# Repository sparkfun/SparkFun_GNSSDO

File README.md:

SparkPNT SXT / SXT-D
========================================

[*SparkPNT SXT (GNSSDO)*](https://www.sparkpnt.com/products/sxt-gnssdo)

Designed and manufactured in Boulder, Colorado, USA, the SparkPNT SXT GNSS Disciplined Oscillator (GNSSDO) and SXT-D GNSS Disciplined Oscillator Plus (GNSSDO+) are the perfect solution for your high-precision timing needs. Based around the multi-constellation, multi-frequency, L5-ready mosaic-T from Septentrio, these are our most accurate GNSS timing products to date. They feature a disciplined 10MHz oscillator: Digitally-Controlled Temperature-Controlled Crystal Oscillator (DCTCXO) on the SXT; Digitally-Controlled Double-Oven Crystal Oscillator (OCXO) on the SXT-D. The mosaic-T also has built-in on-module support for the Fugro AtomiChron L-band timing service.

Under the hood, the SXT and SXT-D are based on the mosaic-T GNSS module from Septentrio, plus the Espressif ESP32-WROVER processor (16MB flash, 8MB PSRAM). The mosaic-T has USB-C connectivity (with Ethernet-over-USB), multiple UARTs and supports full Ethernet connectivity. You can connect the mosaic-T directly to your Ethernet network - our product supports Power-over-Ethernet too. The ESP32 rides shotgun: disciplining the digitally-controlled oscillator and controlling the OLED display. Remote configuration is possible, the ESP32 console can be accessed via TCP. The SXT and SXT-D have multiple power options including USB-C, PoE and 9V-36V DC, making it easy to connect them to a battery-backed supply.

RTK Not Supported
--------------
The mosaic-T is a superb GNSS module designed for highly accurate timing applications. **But it does not support RTK. It can not be used as a RTK Rover or Base. RTCM output is not supported.**

Documentation
--------------

- **[Product Manual](http://docs.sparkfun.com/SparkFun_GNSSDO/)** - Product manual for the SXT(-D) GNSSDO(+) hosted by GitHub pages.<br>

*Need to download or print our hookup guide?*

- [Print *(Print to PDF)* from Single-Page View](http://docs.sparkfun.com/SparkFun_GNSSDO/print_view)

Firmware Update
-------------------

The **[/Firmware/Binaries](https://github.com/sparkfun/SparkFun_GNSSDO/tree/main/Firmware/Binaries)** folder contains the firmware binaries.

You can update or reload the firmware using the [SparkFun RTK Firmware Uploader](https://github.com/sparkfun/SparkFun_RTK_Firmware_Uploader).

Repository Contents
-------------------

- **[/docs](/docs/)** - Online documentation files
    - [assets](/docs/assets/) - Assets files
        - [board_files](/docs/assets/board_files/) - Files for the product design
            - [SXT Schematic](/docs/assets/board_files/schematic.pdf) (.pdf)
            - [SXT-D Schematic](/docs/assets/board_files/SparkPNT_GNSSDO_Plus_schematic) (.pdf)
            - [Dimensions](/docs/assets/board_files/dimensions.png) (.png)
            - [SXT KiCad files](/docs/assets/board_files/kicad_files.zip) (.zip)
            - [SXT-D KiCad files](/docs/assets/board_files/kicad_files_GNSSDO_Plus.zip) (.zip)
        - [img/hookup_guide/](/docs/assets/img/hookup_guide/) - Images for hookup guide documentation
- **[/Hardware](/Hardware/)** - KiCad design files
- **[/Hardware/Production](/Hardware/Production/)** - PCB panel production files
- **[/Front_Sticker](/Front_Sticker/)** - DXF and PDF files for the front sticker
- **[/Rear_Sticker](/Rear_Sticker/)** - DXF and PDF files for the rear sticker
- **[/Firmware](/Firmware/)** - Arduino source code and binaries for the firmware which runs on the ESP32-WROVER
- **[/Test_Sketches](/Test_Sketches/)** - Additional code used to validate and test the SXT
- **[/Documents](/Documents/)** - Component datasheets etc.

Product Variants
----------------

- [SXT](https://www.sparkpnt.com/products/sxt-gnssdo)- SXT (GNSSDO) v1.0, Initial Release
- [SXT-D](https://www.sparkpnt.com/products/sxt-d-gnssdo)- SXT-D (GNSSDO+) v1.0, Initial Release

Version History
---------------

- [v10](https://github.com/sparkfun/SparkFun_GNSSDO/releases/tag/v10) - Initial Release

License Information
-------------------

This product is ***open source***!

Please review the [LICENSE.md](./LICENSE.md) file for license information.

If you have any questions or concerns about licensing, please contact technical support on our [SparkPNT forums](https://community.sparkpnt.com).

Distributed as-is; no warranty is given.

- Your friends at SparkPNT.

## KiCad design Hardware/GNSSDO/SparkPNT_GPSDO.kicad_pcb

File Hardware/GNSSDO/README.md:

SparkPNT GNSSDO Design Files
=====================================

The files here are the KiCad schematic and PCB design files from SparkFun Electronics.

KiCad can be downloaded [here](https://www.kicad.org/).

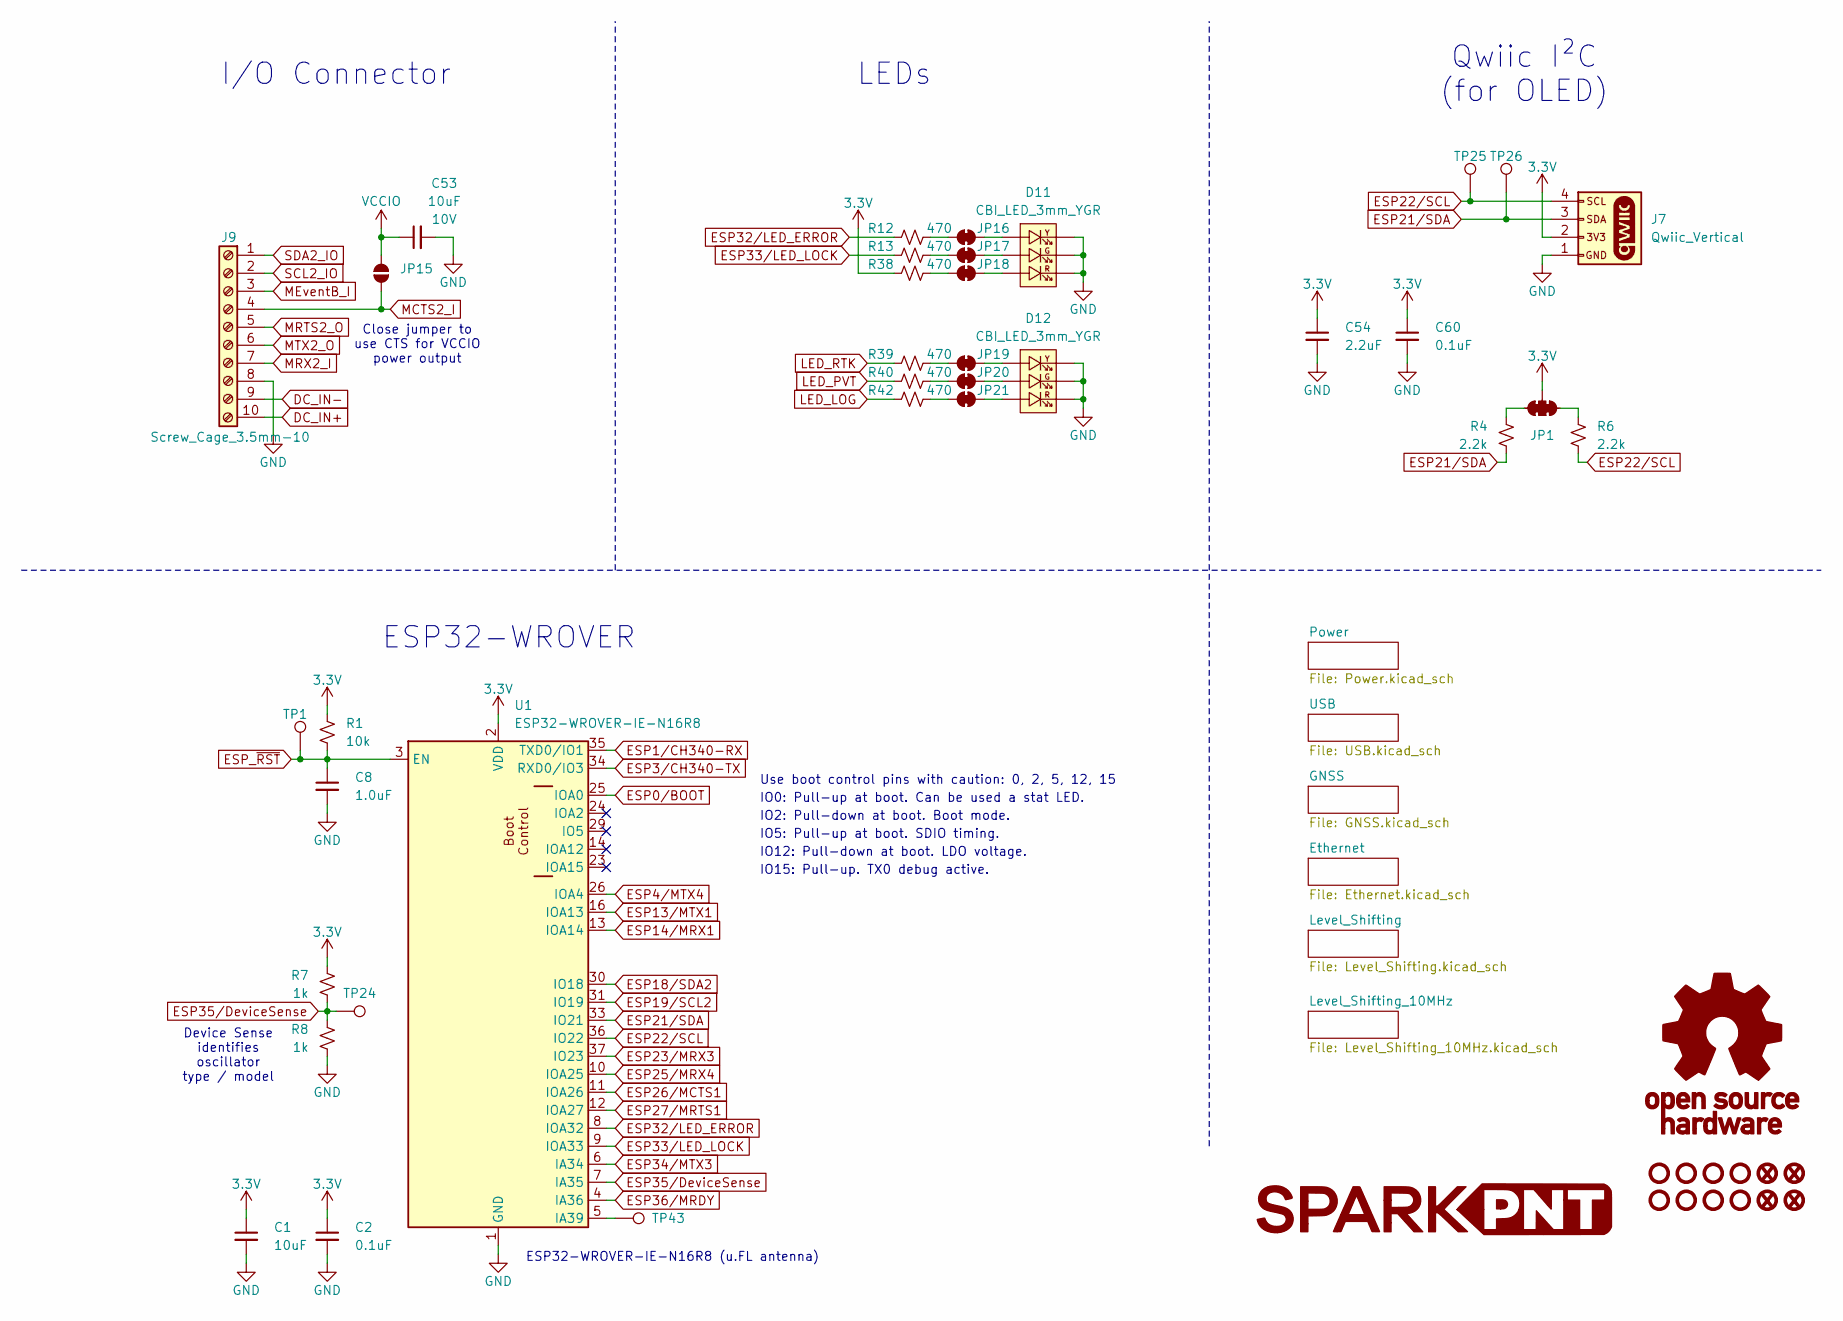
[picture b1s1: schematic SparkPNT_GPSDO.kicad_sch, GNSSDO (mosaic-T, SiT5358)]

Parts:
C1: 10uF; C_0603_1608Metric; Voltage 6.3V; Tolerance 20%
C2, C60: 0.1uF; C_0603_1608Metric; Voltage 25V; Tolerance 20%
C8: 1.0uF; C_0603_1608Metric; Voltage 16V; Tolerance 10%
C53: 10uF; C_0603_1608Metric; Voltage 10V; Tolerance 20%
C54: 2.2uF; C_0603_1608Metric; Voltage 10V; Tolerance 20%
D11, D12: CBI_LED_3mm_YGR; CBI_LED_Triple_3mm_PTH
FID1, FID2, FID3, FID4: Fiducial_0.5mm; Fiducial_0.5mm_Mask1mm
G1: OSHW_Logo; Creative_Commons_License
G2: LOGO
J7: Qwiic_Vertical; JST_1x04_P1.0mm_Vertical_SMD
J9: Screw_Cage_3.5mm-10; ScrewCage_1x10_P3.5mm_Horizontal
JP1: Jumper_3_NC-2_Trace
JP15: Jumper_2_NO
JP16, JP17, JP18, JP19, JP20, JP21: Jumper_2_NC_Trace
R1: 10k; R_0603_1608Metric
R4, R6: 2.2k; R_0603_1608Metric
R7, R8: 1k; R_0603_1608Metric
R12, R13, R38, R39, R40, R42: 470; R_0603_1608Metric
ST1, ST2, ST3, ST4, ST5, ST6, ST7, ST8: Standoff
TP1, TP24, TP25, TP26, TP43: PTH; 1x01_P2.54mm
U1: ESP32-WROVER-IE-N16R8; ESP32-WROVER-E-IE

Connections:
3.3V: C1.1, C2.1, C54.1, C60.1, J7.2, JP1.2 (B), R1.2, R7.2, R38.1, U1.2 (VDD); also elsewhere on the board
DC_IN+: J9.10 (Pin_1); also elsewhere on the board
DC_IN-: J9.9 (Pin_1); also elsewhere on the board
ESP0/BOOT: U1.25 (IOA0); also elsewhere on the board
ESP1/CH340-RX: U1.35 (TXD0/IO1); also elsewhere on the board
ESP3/CH340-TX: U1.34 (RXD0/IO3); also elsewhere on the board
ESP4/MTX4: U1.26 (IOA4); also elsewhere on the board
ESP13/MTX1: U1.16 (IOA13); also elsewhere on the board
ESP14/MRX1: U1.13 (IOA14); also elsewhere on the board
ESP18/SDA2: U1.30 (IO18); also elsewhere on the board
ESP19/SCL2: U1.31 (IO19); also elsewhere on the board
ESP21/SDA: J7.3, R4.2, TP26.1 (1_1), U1.33 (IO21)
ESP22/SCL: J7.4, R6.2, TP25.1 (1_1), U1.36 (IO22)
ESP23/MRX3: U1.37 (IO23); also elsewhere on the board
ESP25/MRX4: U1.10 (IOA25); also elsewhere on the board
ESP26/MCTS1: U1.11 (IOA26); also elsewhere on the board
ESP27/MRTS1: U1.12 (IOA27); also elsewhere on the board
ESP32/LED_ERROR: R12.1, U1.8 (IOA32)
ESP33/LED_LOCK: R13.1, U1.9 (IOA33)
ESP34/MTX3: U1.6 (IA34); also elsewhere on the board
ESP35/DeviceSense: R7.1, R8.2, TP24.1 (1_1), U1.7 (IA35)
ESP36/MRDY: U1.4 (IA36); also elsewhere on the board
ESP_~RST: C8.1, R1.1, TP1.1 (1_1), U1.3 (EN); also elsewhere on the board
GND: C1.2, C2.2, C8.2, C53.2, C54.2, C60.2, D11.CATHODE_1, D11.CATHODE_2, D11.CATHODE_3, D12.CATHODE_1, D12.CATHODE_2, D12.CATHODE_3, J7.1, J9.8 (Pin_1), R8.1, U1.1 (GND), U1.15 (GND), U1.38 (GND), U1.39.1 (GND), U1.39.2 (GND), U1.39.3 (GND), U1.39.4 (GND), U1.39.5 (GND), U1.39.6 (GND), U1.39.7 (GND), U1.39.8 (GND), U1.39.9 (GND); also elsewhere on the board
LED_LOG: R42.1; also elsewhere on the board
LED_PVT: R40.1; also elsewhere on the board
LED_RTK: R39.1; also elsewhere on the board
MCTS2_I: J9.4, JP15.1 (A); also elsewhere on the board
MEventB_I: J9.3; also elsewhere on the board
MRTS2_O: J9.5 (Pin_3); also elsewhere on the board
MRX2_I: J9.7 (Pin_2); also elsewhere on the board
MTX2_O: J9.6 (Pin_4); also elsewhere on the board
unnamed: JP1.1 (A), R6.1
unnamed: JP1.3 (C), R4.1
unnamed: JP16.1 (A), R12.2
unnamed: D11.ANODE_1, JP16.2 (B)
unnamed: JP17.1 (A), R13.2
unnamed: D11.ANODE_2, JP17.2 (B)
unnamed: JP18.1 (A), R38.2
unnamed: D11.ANODE_3, JP18.2 (B)
unnamed: JP19.1 (A), R39.2
unnamed: D12.ANODE_1, JP19.2 (B)
unnamed: JP20.1 (A), R40.2
unnamed: D12.ANODE_2, JP20.2 (B)
unnamed: JP21.1 (A), R42.2
unnamed: D12.ANODE_3, JP21.2 (B)
unnamed: TP43.1 (1_1), U1.5 (IA39)
SCL2_IO: J9.2; also elsewhere on the board
SDA2_IO: J9.1; also elsewhere on the board
VCCIO: C53.1, JP15.2 (B); also elsewhere on the board

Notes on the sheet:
IO15: Pull-up. TX0 debug active.
IO2: Pull-down at boot. Boot mode.
ESP32-WROVER
IO0: Pull-up at boot. Can be used a stat LED.
LEDs
Qwiic I²C (for OLED)
Device Sense identifies oscillator type / model
Close jumper to use CTS for VCCIO power output
IO5: Pull-up at boot. SDIO timing.
I/O Connector
Use boot control pins with caution: 0, 2, 5, 12, 15
ESP32-WROVER-IE-N16R8 (u.FL antenna)
IO12: Pull-down at boot. LDO voltage.

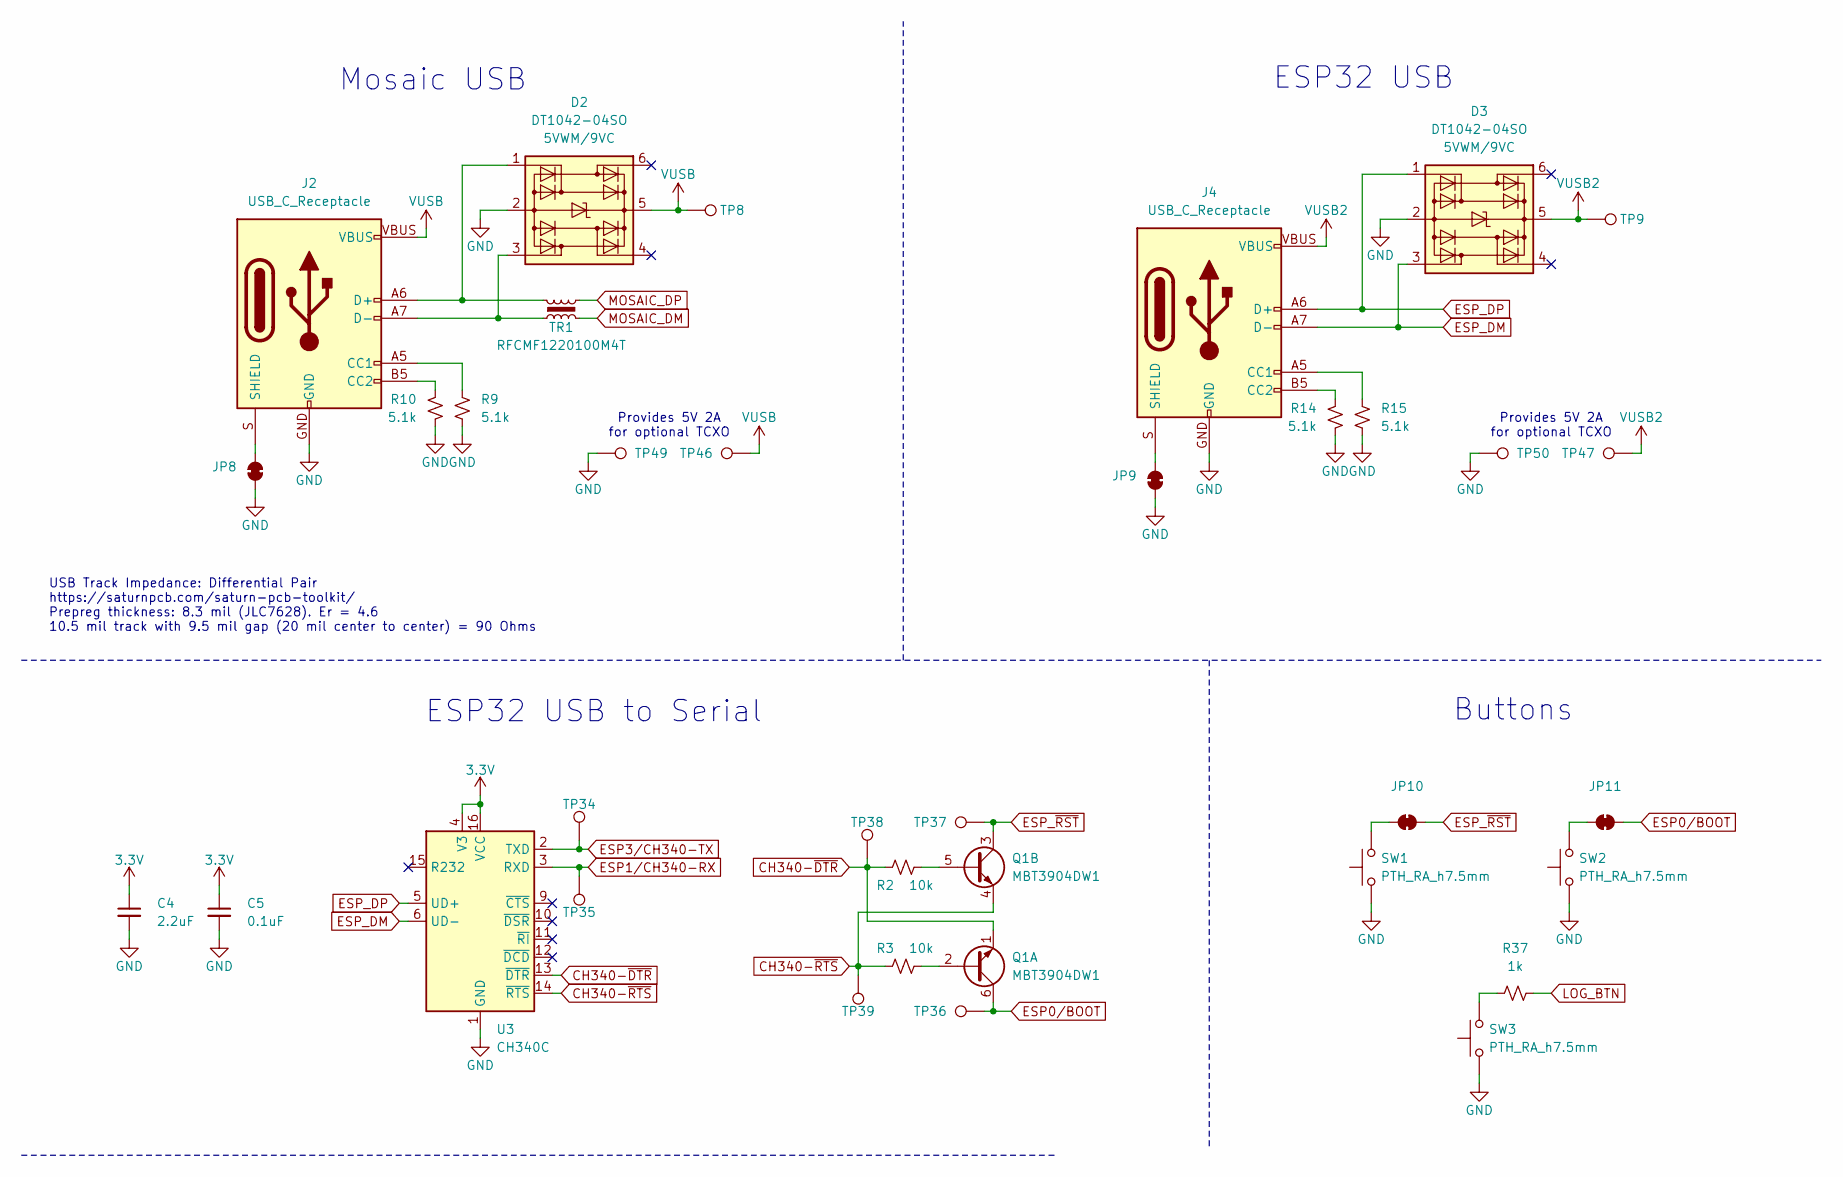
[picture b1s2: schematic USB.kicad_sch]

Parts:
C4: 2.2uF; C_0603_1608Metric; Voltage 10V; Tolerance 20%
C5: 0.1uF; C_0603_1608Metric; Voltage 25V; Tolerance 20%
D2, D3: DT1042-04SO; SOT23-6; Rating 5VWM/9VC
J2, J4: USB_C_Receptacle; USB-C_16
JP8, JP9, JP10, JP11: Jumper_2_NC_Trace
Q1: MBT3904DW1; SOT-363_SC-70-6
R2, R3: 10k; R_0603_1608Metric
R9, R10, R14, R15: 5.1k; R_0603_1608Metric
R37: 1k; R_0603_1608Metric
SW1, SW2, SW3: PTH_RA_h7.5mm; Push_PTH_RA_8-020_h7.5mm; Mfg Part# 8-020 TS H = 7.5mm
TP8, TP9, TP34, TP35, TP36, TP37, TP38, TP39, TP46, TP47, TP49, TP50: PTH; 1x01_P2.54mm
TR1: RFCMF1220100M4T; Choke_100MHz_USB
U3: CH340C; SO-16

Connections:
3.3V: C4.1, C5.1, U3.4 (V3), U3.16 (VCC); also elsewhere on the board
CH340-~DTR: Q1.1 (E1), R2.1, TP38.1 (1_1), U3.13 (~DTR)
CH340-~RTS: Q1.4 (E2), R3.1, TP39.1 (1_1), U3.14 (~RTS)
ESP0/BOOT: JP11.2 (B), Q1.6 (C1), TP36.1 (1_1); also elsewhere on the board
ESP1/CH340-RX: TP35.1 (1_1), U3.3 (RXD); also elsewhere on the board
ESP3/CH340-TX: TP34.1 (1_1), U3.2 (TXD); also elsewhere on the board
ESP_DM: D3.3 (I/O2), J4.A7 (D-), J4.B7 (D-), U3.6 (UD-)
ESP_DP: D3.1 (I/O1), J4.A6 (D+), J4.B6 (D+), U3.5 (UD+)
ESP_~RST: JP10.2 (B), Q1.3 (C2), TP37.1 (1_1); also elsewhere on the board
GND: C4.2, C5.2, D2.2 (GND), D3.2 (GND), J2.GND, J4.GND, JP8.1 (A), JP9.1 (A), R9.2, R10.2, R14.2, R15.2, SW1.1, SW2.1, SW3.1, TP49.1 (1_1), TP50.1 (1_1), U3.1 (GND); also elsewhere on the board
LOG_BTN: R37.2; also elsewhere on the board
MOSAIC_DM: TR1.2; also elsewhere on the board
MOSAIC_DP: TR1.4; also elsewhere on the board
unnamed: D2.1 (I/O1), J2.A6 (D+), J2.B6 (D+), TR1.3
unnamed: D2.3 (I/O2), J2.A7 (D-), J2.B7 (D-), TR1.1
unnamed: J2.A5 (CC1), R9.1
unnamed: J2.B5 (CC2), R10.1
unnamed: J2.S (SHIELD), JP8.2 (B)
unnamed: J4.A5 (CC1), R15.1
unnamed: J4.B5 (CC2), R14.1
unnamed: J4.S (SHIELD), JP9.2 (B)
unnamed: JP10.1 (A), SW1.2
unnamed: JP11.1 (A), SW2.2
unnamed: Q1.2 (B1), R3.2
unnamed: Q1.5 (B2), R2.2
unnamed: R37.1, SW3.2
VUSB: D2.5 (VCC), J2.VBUS, TP8.1 (1_1), TP46.1 (1_1); also elsewhere on the board
VUSB2: D3.5 (VCC), J4.VBUS, TP9.1 (1_1), TP47.1 (1_1); also elsewhere on the board

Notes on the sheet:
ESP32 USB to Serial
Mosaic USB
Provides 5V 2A for optional TCXO
Buttons
ESP32 USB
USB Track Impedance: Differential Pair https://saturnpcb.com/saturn-pcb-toolkit/ Prepreg thickness: 8.3 mil (JLC7628). Er = 4.6 10.5 mil track with 9.5 mil gap (20 mil center to center) = 90 Ohms

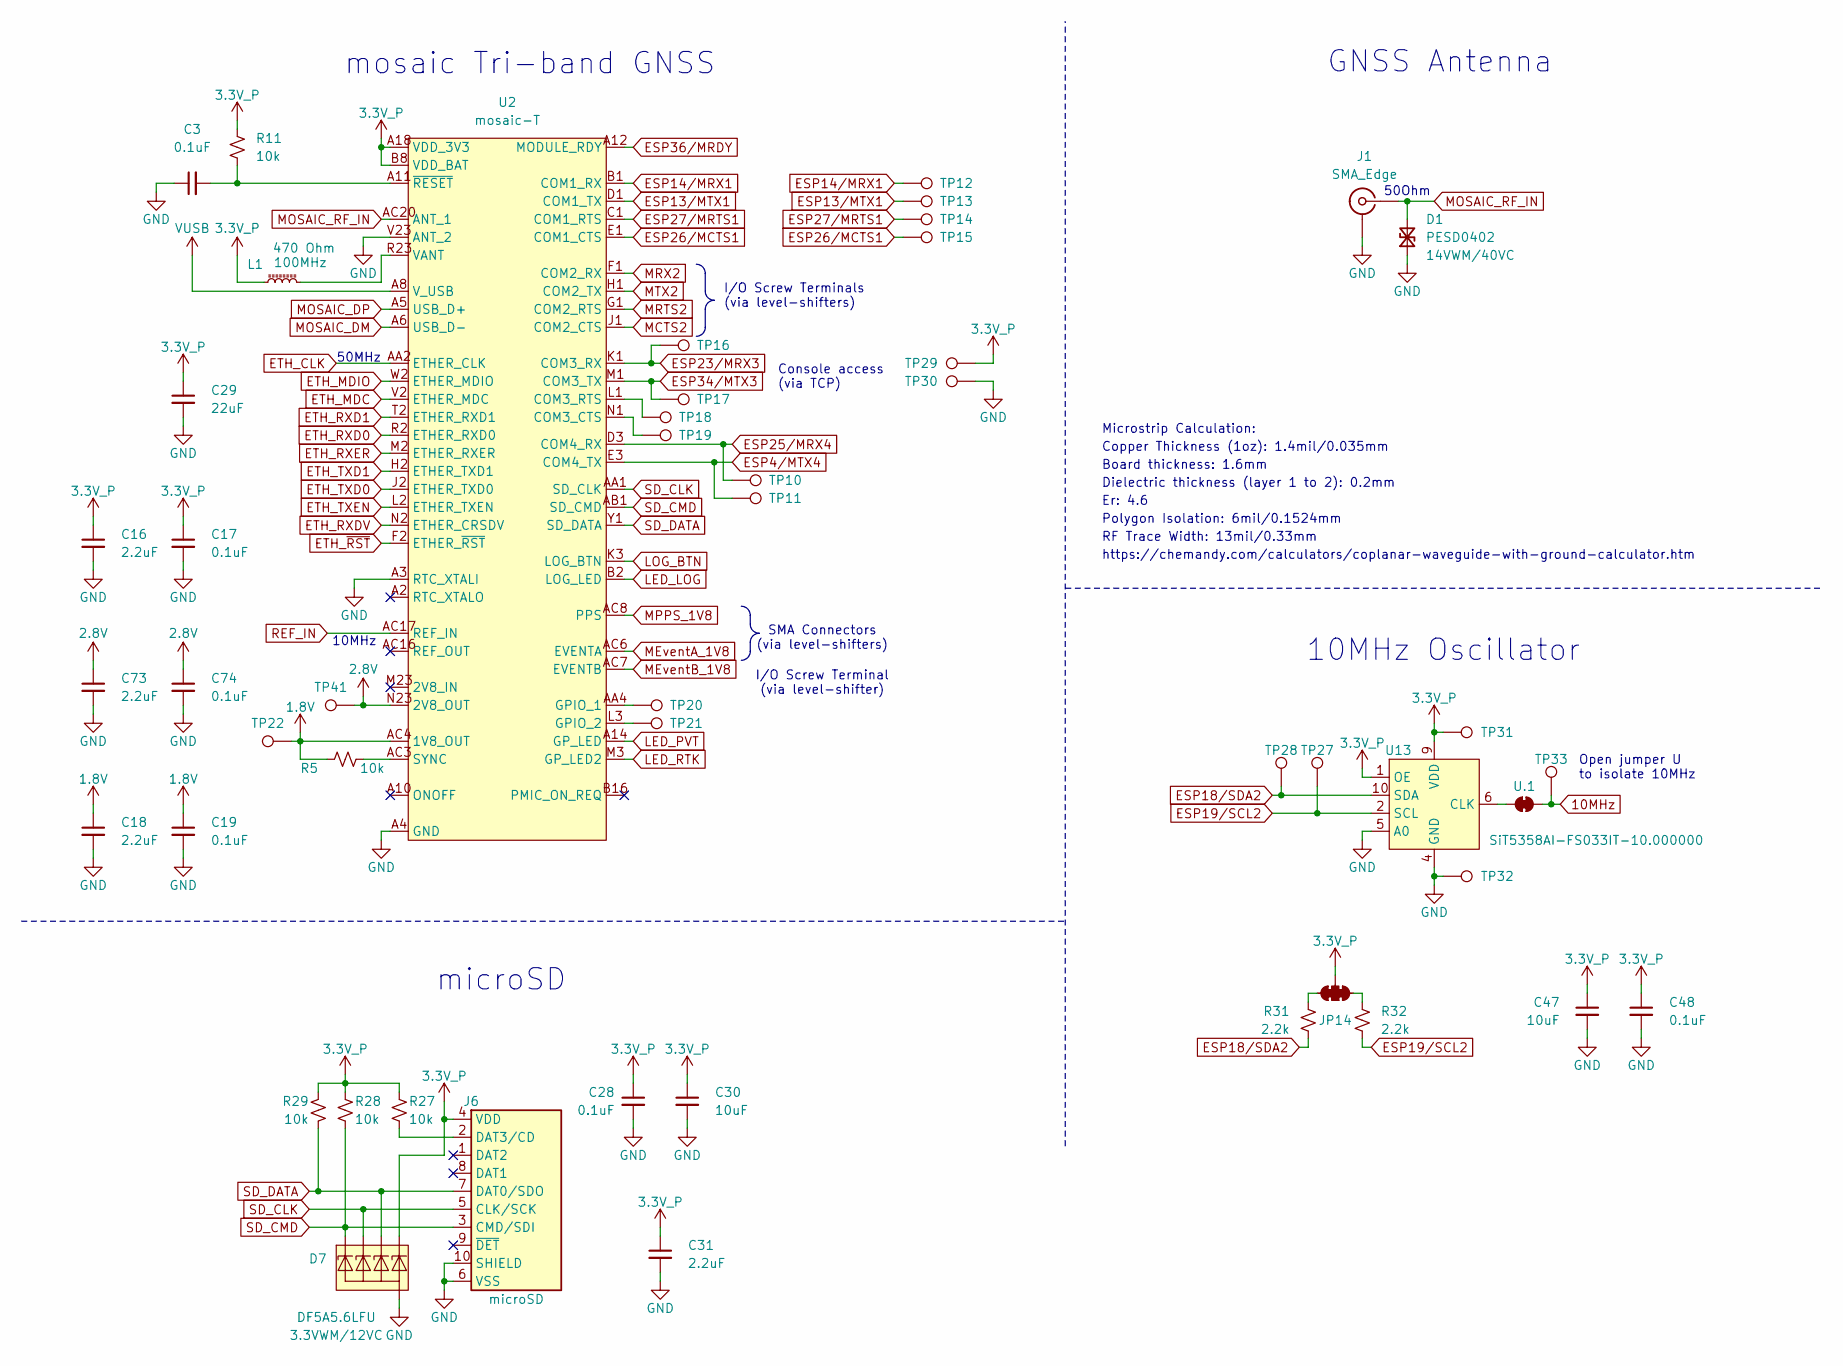
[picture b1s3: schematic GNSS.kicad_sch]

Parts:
C3, C17, C19, C28, C48, C74: 0.1uF; C_0603_1608Metric; Voltage 25V; Tolerance 20%
C16, C18, C31, C73: 2.2uF; C_0603_1608Metric; Voltage 10V; Tolerance 20%
C29: 22uF; C_0603_1608Metric; Voltage 6.3V; Tolerance 20%
C30, C47: 10uF; C_0603_1608Metric; Voltage 10V; Tolerance 20%
D1: PESD0402; C_0402_1005Metric; Rating 14VWM/40VC
D7: DF5A5.6LFU; SOT-353; Rating 3.3VWM/12VC
J1: SMA_Edge; SMA_Edge_6.3mm
J6: microSD; microSD_External_Pin
JP14: Jumper_3_NC-2_Trace
L1: 470 Ohm; C_0603_1608Metric
R5, R11, R27, R28, R29: 10k; R_0603_1608Metric
R31, R32: 2.2k; R_0603_1608Metric
TP10, TP11, TP12, TP13, TP14, TP15, TP16, TP17, TP18, TP19, TP20, TP21, TP22, TP27, TP28, TP29, TP30, TP31, TP32, TP33, TP41: PTH; 1x01_P2.54mm
U2: mosaic-T; Septentrio_mosaic_LGA
U13: SiT5358AI-FS033IT-10.000000; Ceramic_QFN_5.0x3.2mm-10
U.1: Jumper_2_NC_Trace

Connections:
1.8V: C18.1, C19.1, R5.1, TP22.1 (1_1), U2.AC4 (1V8_OUT); also elsewhere on the board
2.8V: C73.1, C74.1, TP41.1 (1_1), U2.N23 (2V8_OUT); also elsewhere on the board
3.3V_P: C16.1, C17.1, C28.1, C29.1, C30.1, C31.1, C47.1, C48.1, D7.5 (K4), J6.4 (VDD), JP14.2 (B), L1.1, R11.1, R27.1, R28.1, R29.1, TP29.1 (1_1), TP31.1 (1_1), U2.A18 (VDD_3V3), U2.A19 (VDD_3V3), U2.A20 (VDD_3V3), U2.B8 (VDD_BAT), U2.B18 (VDD_3V3), U2.B19 (VDD_3V3), U2.B20 (VDD_3V3), U2.C18 (VDD_3V3), U2.C19 (VDD_3V3), U2.C20 (VDD_3V3), U13.1 (OE), U13.9 (VDD); also elsewhere on the board
10MHz: TP33.1 (1_1), U.1.2 (B); also elsewhere on the board
ESP4/MTX4: TP11.1 (1_1), U2.E3 (COM4_TX); also elsewhere on the board
ESP13/MTX1: TP13.1 (1_1), U2.D1 (COM1_TX); also elsewhere on the board
ESP14/MRX1: TP12.1 (1_1), U2.B1 (COM1_RX); also elsewhere on the board
ESP18/SDA2: R31.1, TP28.1 (1_1), U13.10 (SDA); also elsewhere on the board
ESP19/SCL2: R32.1, TP27.1 (1_1), U13.2 (SCL); also elsewhere on the board
ESP23/MRX3: TP16.1 (1_1), U2.K1 (COM3_RX); also elsewhere on the board
ESP25/MRX4: TP10.1 (1_1), U2.D3 (COM4_RX); also elsewhere on the board
ESP26/MCTS1: TP15.1 (1_1), U2.E1 (COM1_CTS); also elsewhere on the board
ESP27/MRTS1: TP14.1 (1_1), U2.C1 (COM1_RTS); also elsewhere on the board
ESP34/MTX3: TP17.1 (1_1), U2.M1 (COM3_TX); also elsewhere on the board
ESP36/MRDY: U2.A12 (MODULE_RDY); also elsewhere on the board
ETH_CLK: U2.AA2 (ETHER_CLK); also elsewhere on the board
ETH_MDC: U2.V2 (ETHER_MDC); also elsewhere on the board
ETH_MDIO: U2.W2 (ETHER_MDIO); also elsewhere on the board
ETH_RXD0: U2.R2 (ETHER_RXD0); also elsewhere on the board
ETH_RXD1: U2.T2 (ETHER_RXD1); also elsewhere on the board
ETH_RXDV: U2.N2 (ETHER_CRSDV); also elsewhere on the board
ETH_RXER: U2.M2 (ETHER_RXER); also elsewhere on the board
ETH_TXD0: U2.J2 (ETHER_TXD0); also elsewhere on the board
ETH_TXD1: U2.H2 (ETHER_TXD1); also elsewhere on the board
ETH_TXEN: U2.L2 (ETHER_TXEN); also elsewhere on the board
ETH_~RST: U2.F2 (ETHER_~RST); also elsewhere on the board
GND: C3.1, C16.2, C17.2, C18.2, C19.2, C28.2, C29.2, C30.2, C31.2, C47.2, C48.2, C73.2, C74.2, D1.1 (A1), D7.2 (A), J1.2 (Ext), J6.6 (VSS), J6.10 (SHIELD), TP30.1 (1_1), TP32.1 (1_1), U2.A3 (RTC_XTALI), U2.A4 (GND), U2.A7 (GND), U2.A15 (GND), U2.A16 (GND), U2.A17 (GND), U2.A21 (GND), U2.A22 (GND), U2.A23 (GND), U2.AA13 (GND), U2.AA14 (GND), U2.AA15 (GND), U2.AA16 (GND), U2.AA17 (GND), U2.AA18 (GND), U2.AA19 (GND), U2.AA20 (GND), U2.AA21 (GND), U2.AA22 (GND), U2.AA23 (GND), U2.AB2 (GND), U2.AB3 (GND), U2.AB4 (GND), U2.AB5 (GND), U2.AB6 (GND), U2.AB7 (GND), U2.AB8 (GND), U2.AB13 (GND), U2.AB14 (GND), U2.AB15 (GND), U2.AB16 (GND), U2.AB17 (GND), U2.AB18 (GND), U2.AB19 (GND), U2.AB20 (GND), U2.AB21 (GND), U2.AB22 (GND), U2.AB23 (GND), U2.AC13 (GND), U2.AC15 (GND), U2.AC18 (GND), U2.AC19 (GND), U2.AC21 (GND), U2.AC22 (GND), U2.AC23 (GND), U2.B4 (GND), U2.B5 (GND), U2.B6 (GND), U2.B7 (GND), U2.B13 (GND), U2.B17 (GND), U2.B21 (GND), U2.C4 (GND), U2.C7 (GND), U2.C15 (GND), U2.C16 (GND), U2.C17 (GND), U2.C23 (GND), U2.D2 (GND), U2.D21 (GND), U2.D22 (GND), U2.D23 (GND), U2.E2 (GND), U2.E21 (GND), U2.E22 (GND), U2.E23 (GND), U2.F21 (GND), U2.F22 (GND), U2.F23 (GND), U2.G2 (GND), U2.G21 (GND), U2.G23 (GND), U2.H21 (GND), U2.H22 (GND), U2.H23 (GND), U2.J21 (GND), U2.J22 (GND), U2.J23 (GND), U2.K2 (GND), U2.K21 (GND), U2.K22 (GND), U2.K23 (GND), U2.L21 (GND), U2.L22 (GND), U2.L23 (GND), U2.M21 (GND), U2.M22 (GND), U2.N21 (GND), U2.N22 (GND), U2.P1 (GND), U2.P2 (GND), U2.P3 (GND), U2.P21 (GND), U2.P22 (GND), U2.R3 (GND), U2.R21 (GND), U2.R22 (GND), U2.T21 (GND), U2.T22 (GND), U2.T23 (GND), U2.U2 (GND), U2.U21 (GND), U2.U22 (GND), U2.U23 (GND), U2.V21 (GND), U2.V22 (GND), U2.V23 (ANT_2), U2.W21 (GND), U2.W22 (GND), U2.W23 (GND), U2.Y2 (GND), U2.Y21 (GND), U2.Y22 (GND), U2.Y23 (GND), U13.4 (GND), U13.5 (A0); also elsewhere on the board
LED_LOG: U2.B2 (LOG_LED); also elsewhere on the board
LED_PVT: U2.A14 (GP_LED); also elsewhere on the board
LED_RTK: U2.M3 (GP_LED2); also elsewhere on the board
LOG_BTN: U2.K3 (LOG_BTN); also elsewhere on the board
MCTS2: U2.J1 (COM2_CTS); also elsewhere on the board
MEventA_1V8: U2.AC6 (EVENTA); also elsewhere on the board
MEventB_1V8: U2.AC7 (EVENTB); also elsewhere on the board
MOSAIC_DM: U2.A6 (USB_D-); also elsewhere on the board
MOSAIC_DP: U2.A5 (USB_D+); also elsewhere on the board
MOSAIC_RF_IN: D1.2 (A2), J1.1 (In), U2.AC20 (ANT_1)
MPPS_1V8: U2.AC8 (PPS); also elsewhere on the board
MRTS2: U2.G1 (COM2_RTS); also elsewhere on the board
MRX2: U2.F1 (COM2_RX); also elsewhere on the board
MTX2: U2.H1 (COM2_TX); also elsewhere on the board
unnamed: J6.2 (DAT3/CD), R27.2
unnamed: JP14.1 (A), R32.2
unnamed: JP14.3 (C), R31.2
unnamed: TP19.1 (1_1), U2.N1 (COM3_CTS)
unnamed: TP18.1 (1_1), U2.L1 (COM3_RTS)
unnamed: TP20.1 (1_1), U2.AA4 (GPIO_1)
unnamed: TP21.1 (1_1), U2.L3 (GPIO_2)
unnamed: R5.2, U2.AC3 (SYNC)
unnamed: C3.2, R11.2, U2.A11 (~RESET)
unnamed: U13.6 (CLK), U.1.1 (A)
REF_IN: U2.AC17 (REF_IN); also elsewhere on the board
SD_CLK: D7.3 (K2), J6.5 (CLK/SCK), U2.AA1 (SD_CLK)
SD_CMD: D7.1 (K1), J6.3 (CMD/SDI), R28.2, U2.AB1 (SD_CMD)
SD_DATA: D7.4 (K3), J6.7 (DAT0/SDO), R29.2, U2.Y1 (SD_DATA)
VANT: L1.2, U2.P23 (VANT), U2.R23 (VANT)
VUSB: U2.A8 (V_USB); also elsewhere on the board

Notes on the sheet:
Er: 4.6
Polygon Isolation: 6mil/0.1524mm
10MHz
Console access (via TCP)
SMA Connectors (via level-shifters)
10MHz Oscillator
Dielectric thickness (layer 1 to 2): 0.2mm
Board thickness: 1.6mm
Open jumper U to isolate 10MHz
mosaic Tri-band GNSS
Microstrip Calculation:
50Ohm
I/O Screw Terminals (via level-shifters)
https://chemandy.com/calculators/coplanar-waveguide-with-ground-calculator.htm
Copper Thickness (1oz): 1.4mil/0.035mm
I/O Screw Terminal (via level-shifter)
50MHz
GNSS Antenna
microSD
RF Trace Width: 13mil/0.33mm

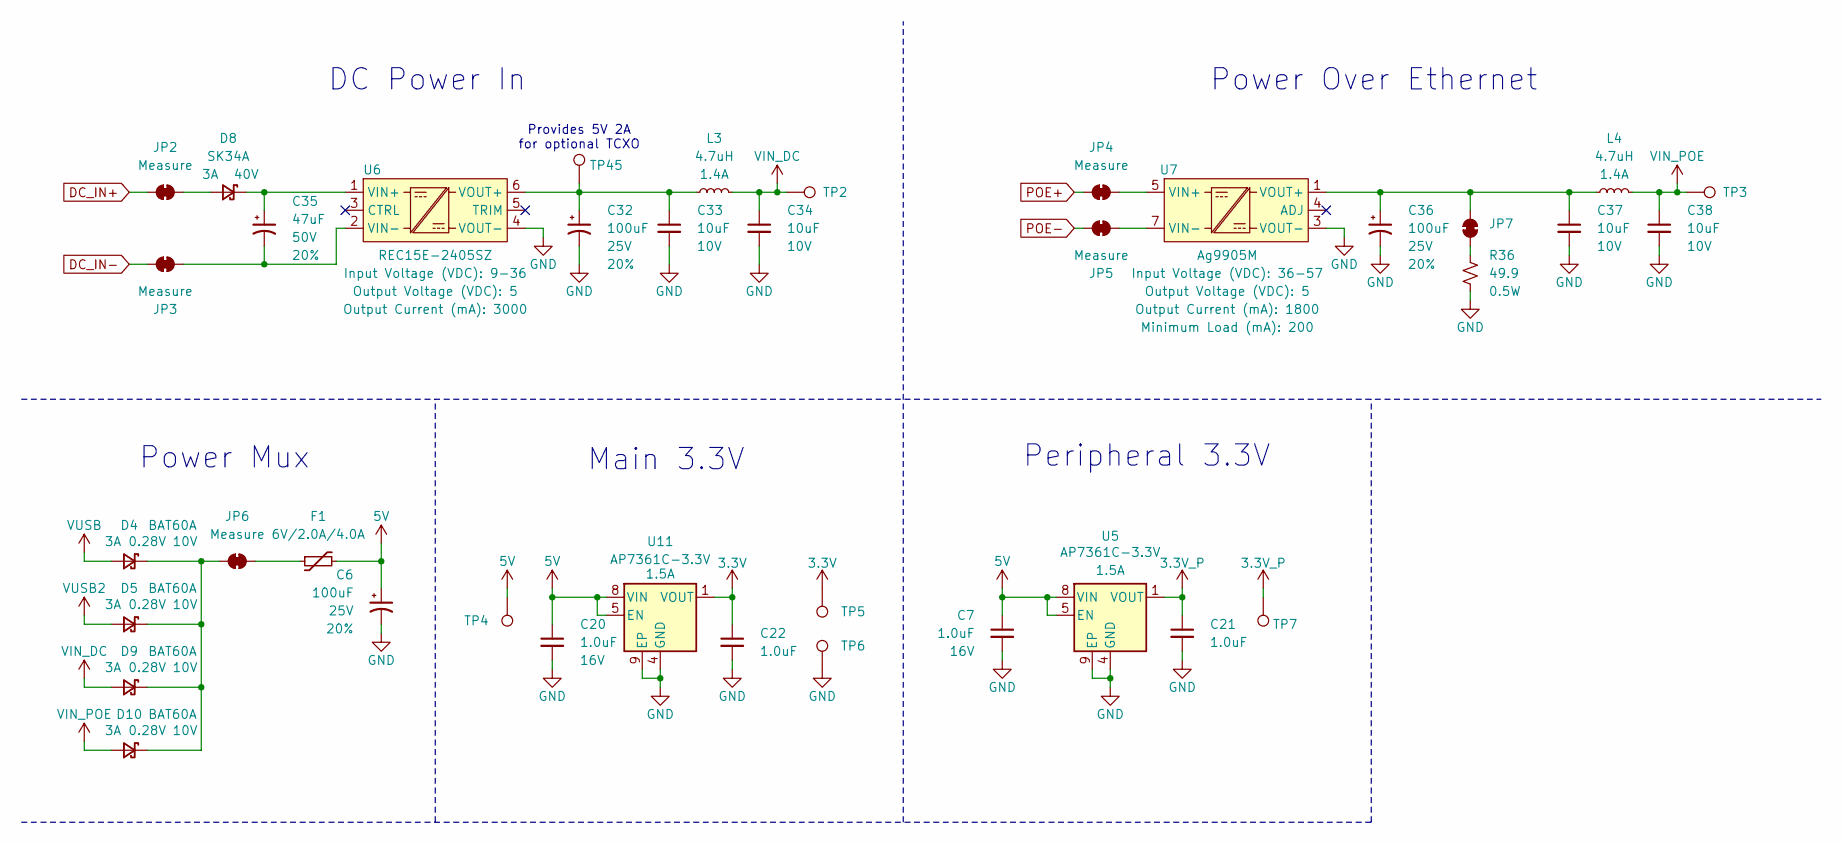
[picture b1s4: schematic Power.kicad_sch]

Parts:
C6, C32, C36: 100uF; Panasonic_D; Voltage 25V; Tolerance 20%
C7, C20, C21, C22: 1.0uF; C_0603_1608Metric; Voltage 16V; Tolerance 10%
C33, C34, C37, C38: 10uF; C_0603_1608Metric; Voltage 10V; Tolerance 20%
C35: 47uF; Panasonic_D; Voltage 50V; Tolerance 20%
D4, D5, D9, D10: BAT60A; SOD-323
D8: SK34A; SMA
F1: 6V/2.0A/4.0A; 1210
JP2, JP3, JP4, JP5, JP6: Measure; Jumper_2_PTH_SMD_Combo-NC
JP7: Jumper_2_NC_Trace
L3, L4: 4.7uH; 1008_2520Metric
R36: 49.9; R_1206_3216Metric; Tolerance 1%
TP2, TP3, TP4, TP5, TP6, TP7, TP45: PTH; 1x01_P2.54mm
U5, U11: AP7361C-3.3V; DFN-8_3x3mm_P0.65mm_EP2.25x1.5mm
U6: REC15E-2405SZ; REC15E; Input Voltage (VDC) 9-36; Output Voltage (VDC) 5
U7: Ag9905M; Ag9900M; Input Voltage (VDC) 36-57; Output Voltage (VDC) 5

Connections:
3.3V: C22.1, TP5.1 (1_1), U11.1 (VOUT); also elsewhere on the board
3.3V_P: C21.1, TP7.1 (1_1), U5.1 (VOUT); also elsewhere on the board
5V: C6.1, C7.1, C20.1, F1.2, TP4.1 (1_1), U5.5 (EN), U5.8 (VIN), U11.5 (EN), U11.8 (VIN); also elsewhere on the board
DC_IN+: JP2.1 (A); also elsewhere on the board
DC_IN-: JP3.1 (A); also elsewhere on the board
GND: C6.2, C7.2, C20.2, C21.2, C22.2, C32.2, C33.2, C34.2, C36.2, C37.2, C38.2, R36.2, TP6.1 (1_1), U5.4 (GND), U5.9 (EP), U6.4 (VOUT-), U7.3 (VOUT-), U11.4 (GND), U11.9 (EP); also elsewhere on the board
unnamed: D8.2 (A), JP2.2 (B)
unnamed: C35.1, D8.1 (K), U6.1 (VIN+)
unnamed: D4.1 (K), D5.1 (K), D9.1 (K), D10.1 (K), JP6.1 (A)
unnamed: C35.2, JP3.2 (B), U6.2 (VIN-)
unnamed: F1.1, JP6.2 (B)
unnamed: JP7.1 (A), R36.1
unnamed: C36.1, C37.1, JP7.2 (B), L4.1, U7.1 (VOUT+), U7.2 (VOUT+)
unnamed: C32.1, C33.1, L3.1, TP45.1 (1_1), U6.6 (VOUT+)
POE+: JP4.1 (A); also elsewhere on the board
POE-: JP5.1 (A); also elsewhere on the board
VIN+: JP4.2 (B), U7.5 (VIN+), U7.6 (VIN+)
VIN-: JP5.2 (B), U7.7 (VIN-), U7.8 (VIN-)
VIN_DC: C34.1, D9.2 (A), L3.2, TP2.1 (1_1)
VIN_POE: C38.1, D10.2 (A), L4.2, TP3.1 (1_1)
VUSB: D4.2 (A); also elsewhere on the board
VUSB2: D5.2 (A); also elsewhere on the board

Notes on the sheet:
Power Over Ethernet
Provides 5V 2A for optional TCXO
DC Power In
Peripheral 3.3V
Power Mux
Main 3.3V

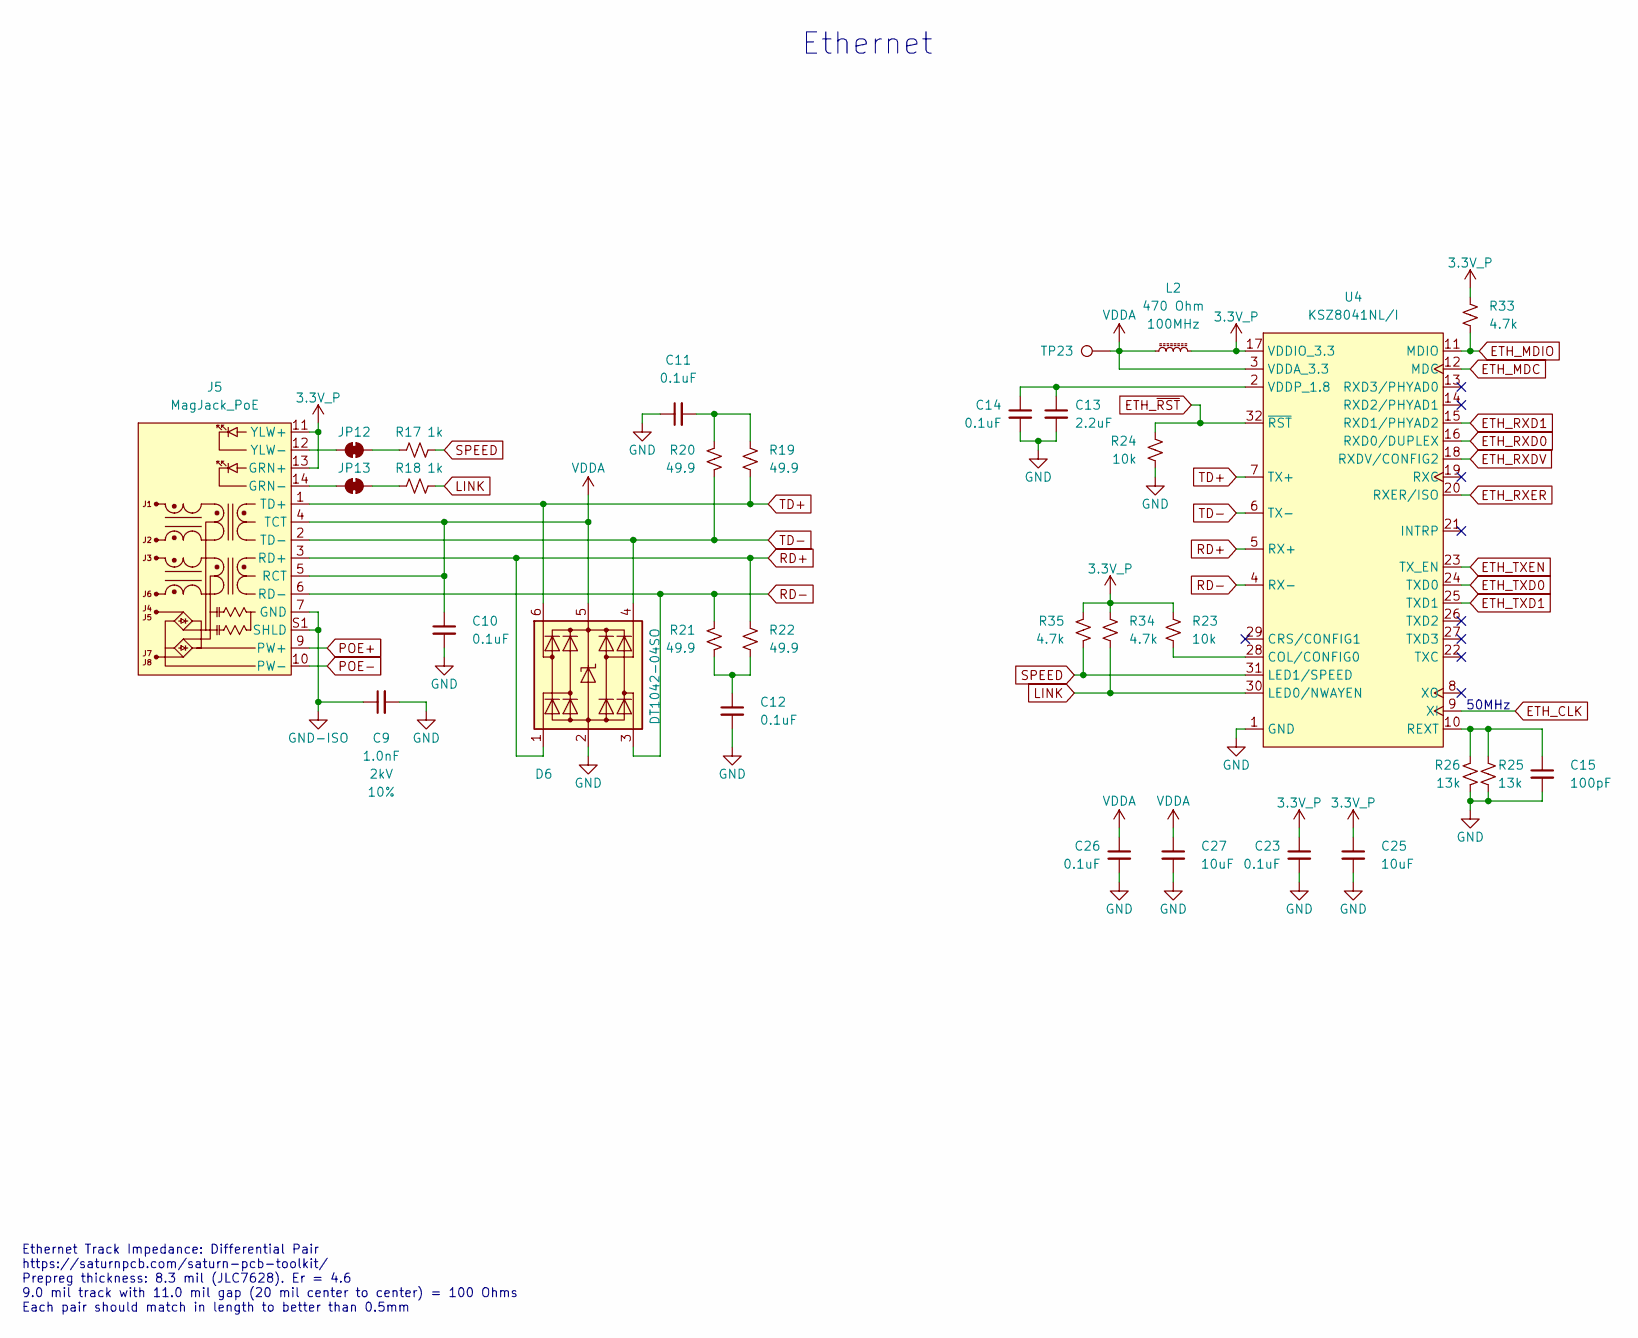
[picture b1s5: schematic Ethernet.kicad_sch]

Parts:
C9: 1.0nF; C_1206_3216Metric; Voltage 2kV; Tolerance 10%
C10, C11, C12, C14, C23, C26: 0.1uF; C_0603_1608Metric; Voltage 25V; Tolerance 20%
C13: 2.2uF; C_0603_1608Metric; Voltage 10V; Tolerance 20%
C15: 100pF; C_0603_1608Metric; Voltage 50V; Tolerance 10%
C25, C27: 10uF; C_0603_1608Metric; Voltage 10V; Tolerance 20%
D6: DT1042-04SO; SOT23-6; Rating 5VWM/9VC
J5: MagJack_PoE; MagJack_PoE_RJ45
JP12, JP13: Jumper_2_NC_Trace
L2: 470 Ohm; C_0603_1608Metric
R17, R18: 1k; R_0603_1608Metric
R19, R20, R21, R22: 49.9; R_0603_1608Metric; Tolerance 1%
R23, R24: 10k; R_0603_1608Metric
R25, R26: 13k; R_0603_1608Metric
R33, R34, R35: 4.7k; R_0603_1608Metric
TP23: PTH; 1x01_P2.54mm
U4: KSZ8041NL/I; QFN-32

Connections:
3.3V_P: C23.1, C25.1, J5.11 (YLW+), J5.13 (GRN+), L2.2, R23.1, R33.2, R34.2, R35.2, U4.17 (VDDIO_3.3); also elsewhere on the board
ETH_CLK: U4.9 (XI); also elsewhere on the board
ETH_MDC: U4.12 (MDC); also elsewhere on the board
ETH_MDIO: R33.1, U4.11 (MDIO); also elsewhere on the board
ETH_RXD0: U4.16 (RXD0/DUPLEX); also elsewhere on the board
ETH_RXD1: U4.15 (RXD1/PHYAD2); also elsewhere on the board
ETH_RXDV: U4.18 (RXDV/CONFIG2); also elsewhere on the board
ETH_RXER: U4.20 (RXER/ISO); also elsewhere on the board
ETH_TXD0: U4.24 (TXD0); also elsewhere on the board
ETH_TXD1: U4.25 (TXD1); also elsewhere on the board
ETH_TXEN: U4.23 (TX_EN); also elsewhere on the board
ETH_~RST: R24.2, U4.32 (~RST); also elsewhere on the board
GND: C9.2, C10.2, C11.1, C12.2, C13.2, C14.2, C15.2, C23.2, C25.2, C26.2, C27.2, D6.2 (GND), R24.1, R25.1, R26.1, U4.1 (GND), U4.EP (GND); also elsewhere on the board
GND-ISO: C9.1, J5.7 (GND), J5.S1 (SHLD), J5.S2 (SHLD)
LINK: R18.2, R34.1, U4.30 (LED0/NWAYEN)
unnamed: C11.2, R19.2, R20.2
unnamed: C12.1, R21.1, R22.1
unnamed: J5.14 (GRN-), JP13.1 (A)
unnamed: J5.12 (YLW-), JP12.1 (A)
unnamed: JP12.2 (B), R17.1
unnamed: JP13.2 (B), R18.1
unnamed: R23.2, U4.28 (COL/CONFIG0)
unnamed: C15.1, R25.2, R26.2, U4.10 (REXT)
unnamed: C13.1, C14.1, U4.2 (VDDP_1.8)
POE+: J5.9 (PW+); also elsewhere on the board
POE-: J5.10 (PW-); also elsewhere on the board
RD+: D6.1 (I/O1), J5.3 (RD+), R22.2, U4.5 (RX+)
RD-: D6.3 (I/O2), J5.6 (RD-), R21.2, U4.4 (RX-)
SPEED: R17.2, R35.1, U4.31 (LED1/SPEED)
TD+: D6.6 (I/O4), J5.1 (TD+), R19.1, U4.7 (TX+)
TD-: D6.4 (I/O3), J5.2 (TD-), R20.1, U4.6 (TX-)
VDDA: C10.1, C26.1, C27.1, D6.5 (VCC), J5.4 (TCT), J5.5 (RCT), L2.1, TP23.1 (1_1), U4.3 (VDDA_3.3)

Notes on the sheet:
50MHz
Ethernet
Ethernet Track Impedance: Differential Pair https://saturnpcb.com/saturn-pcb-toolkit/ Prepreg thickness: 8.3 mil (JLC7628). Er = 4.6 9.0 mil track with 11.0 mil gap (20 mil center to center) = 100 Ohms Each pair should match in length to better than 0.5mm

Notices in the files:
parts and their libraries:
Released under the Creative Commons Attribution Share-Alike 4.0 License
https://creativecommons.org/licenses/by-sa/4.0
